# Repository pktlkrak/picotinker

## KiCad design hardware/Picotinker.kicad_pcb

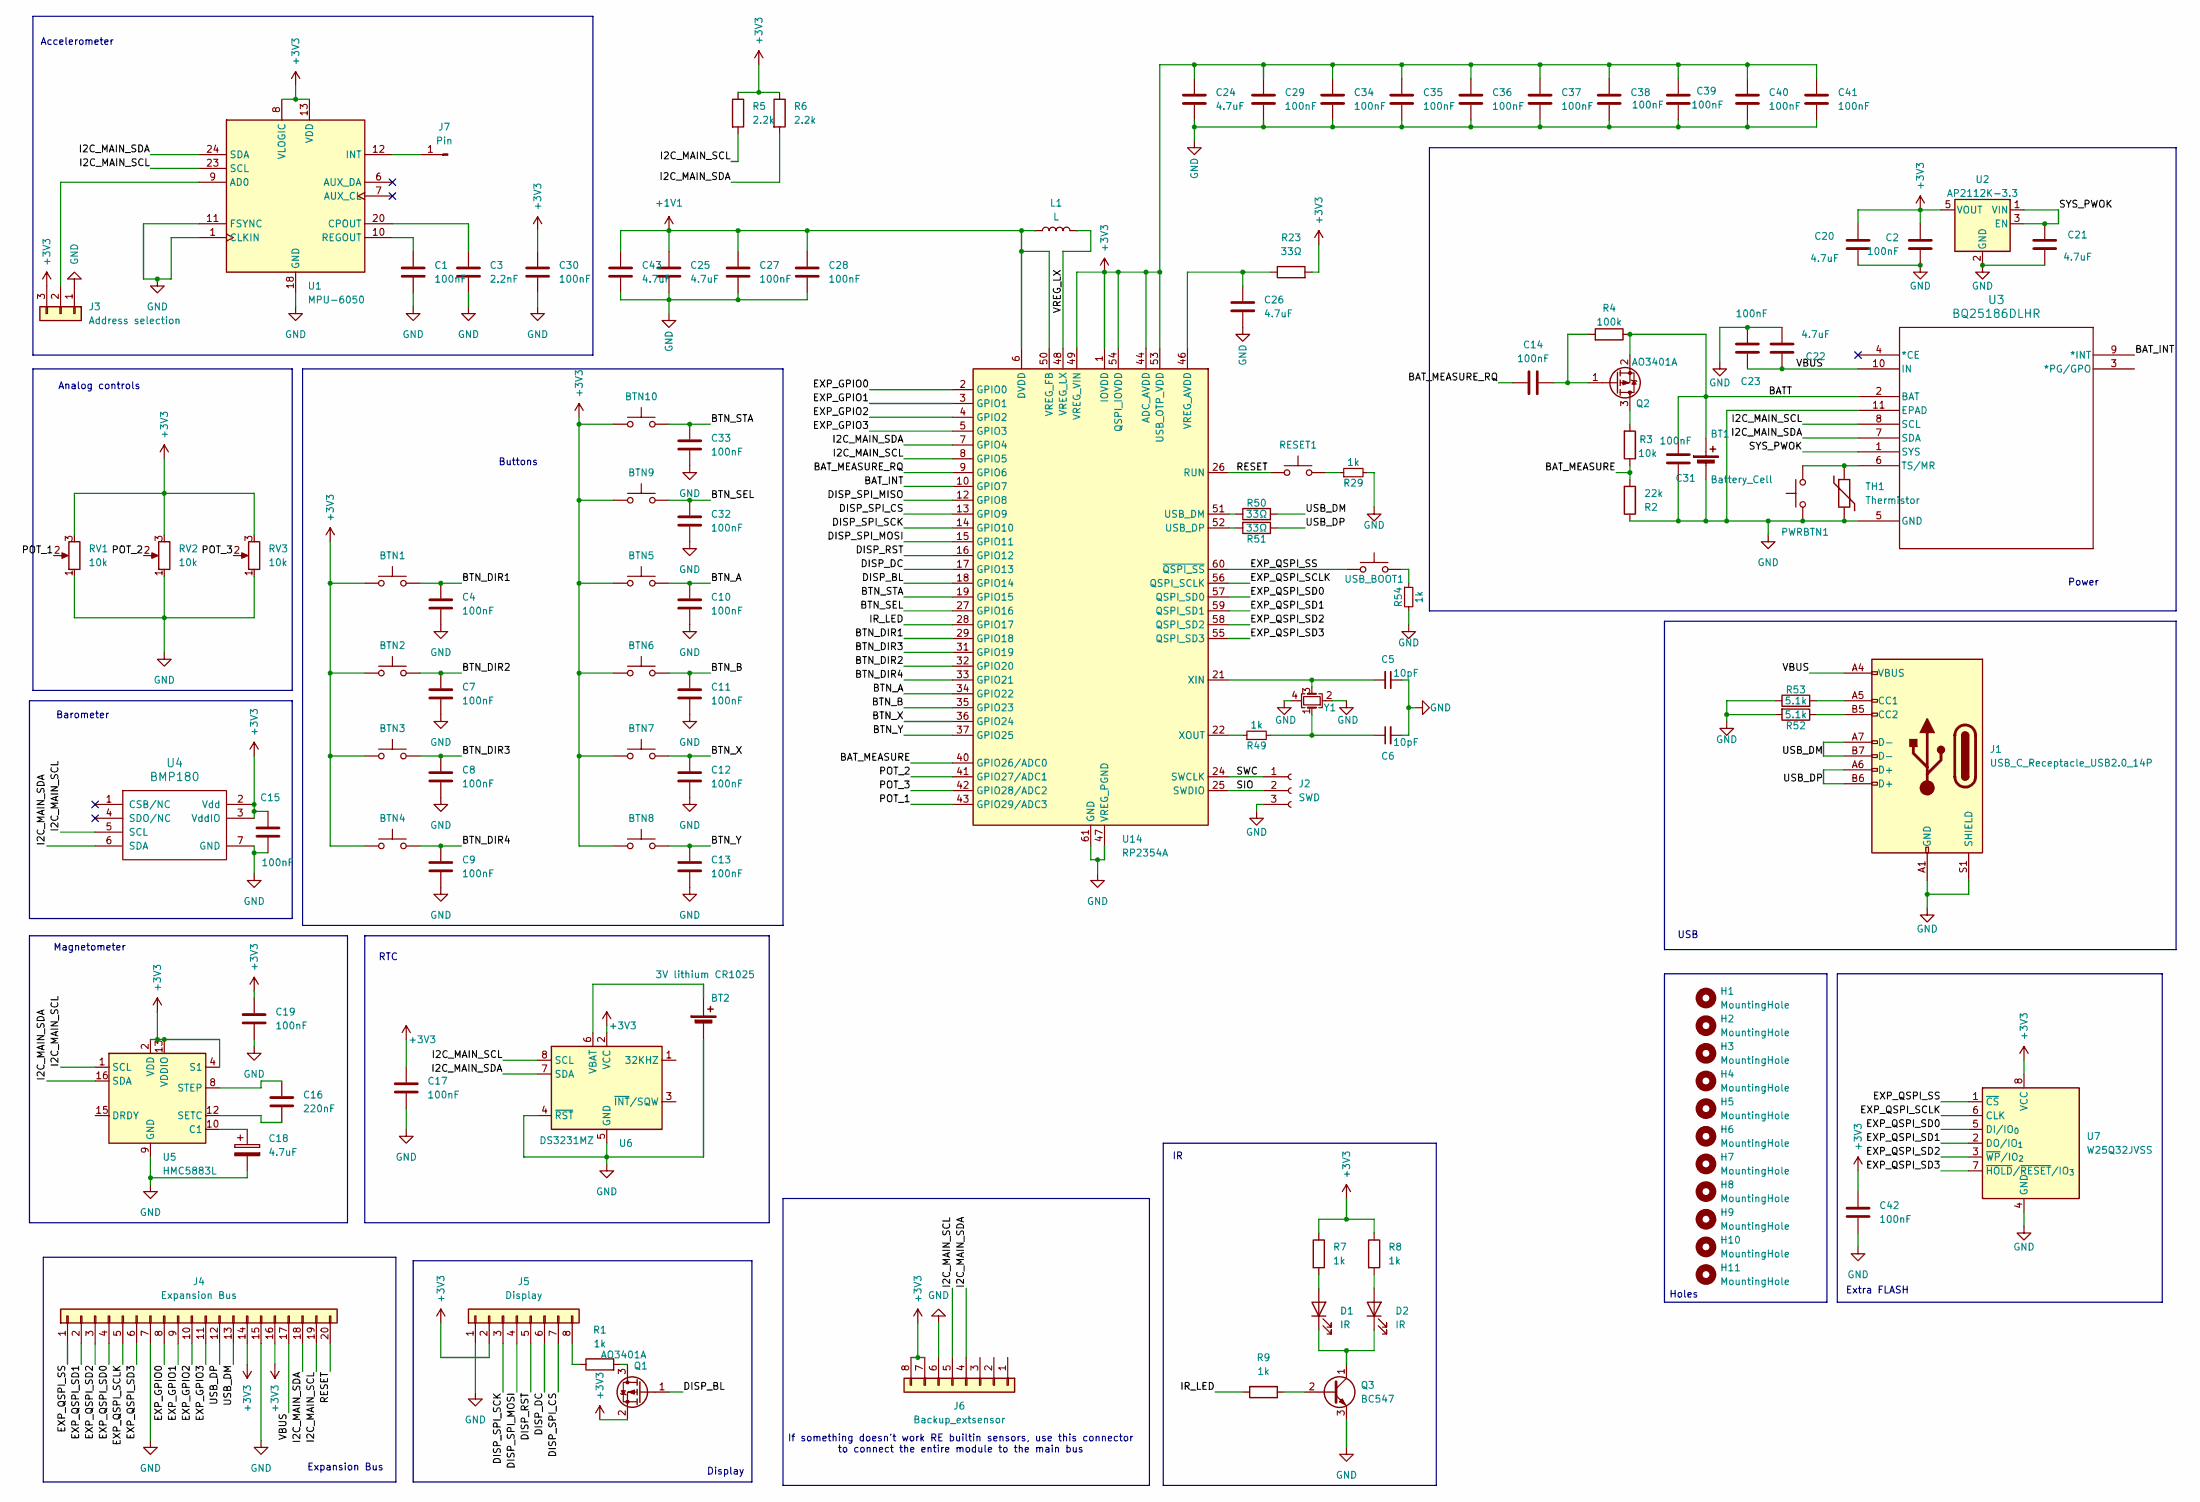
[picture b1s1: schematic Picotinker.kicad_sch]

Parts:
BT1: Battery_Cell; PinHeader_1x02_P2.00mm_Vertical
BT2: 3V lithium CR1025; BatteryHolder_LINX_BAT-HLD-012-SMT
BTN1, BTN2, BTN3, BTN4, BTN5, BTN6, BTN7, BTN8, BTN9, BTN10: SW_Push; SW_PUSH_6mm; MPN KMR241G LFS
C1, C4, C7, C8, C9, C10, C11, C12, C13, C14, C15, C17, C19, C23, C31, C32, C33: 100nF; C_0603_1608Metric
C2, C27, C28, C29, C30, C34, C35, C36, C37, C38, C39, C40, C41, C42: 100nF; C_0603_1608Metric; MPN CL05B104KA5NNNC
C3: 2.2nF; C_0603_1608Metric
C5, C6: 10pF; C_0603_1608Metric; MPN CL10C100JB8NFNC
C16: 220nF; C_0603_1608Metric
C18, C20, C21, C22: 4.7uF; C_1206_3216Metric
C24, C25, C26, C43: 4.7uF; C_0603_1608Metric; MPN GRM155D80E475ME47J
D1, D2: IR; LED_D3.0mm
H1, H2, H3, H4, H5, H6, H7, H8, H9, H10, H11: MountingHole; MountingHole_2.2mm_M2
J1: USB_C_Receptacle_USB2.0_14P; USB_C_Receptacle_XKB_U262-16XN-4BVC11; MPN TYPE-C-31-M-14
J2: SWD; PinHeader_1x03_P2.54mm_Vertical
J3: Address selection; SolderJumper-3_P2.0mm_Open_TrianglePad1.0x1.5mm
J4: Expansion Bus; PinHeader_1x21_P2.54mm_Vertical
J5: Display; PinHeader_1x09_P2.54mm_Vertical
J6: Backup_extsensor; PinHeader_1x08_P2.54mm_Vertical
J7: Pin; Pin_D1.0mm_L10.0mm
L1: L; R_0805_2012Metric; MPN AOTA-B201610S3R3-101-T
PWRBTN1: SW_Push; SW_Tactile_SPST_Angled_PTS645Vx58-2LFS; MPN KMR241G LFS
Q1, Q2: AO3401A; SOT-23
Q3: BC547; SOT-23
R1, R7, R8, R9: 1k; R_0603_1608Metric
R2: 22k; R_0603_1608Metric
R3: 10k; R_0603_1608Metric
R4: 100k; R_0603_1608Metric
R5, R6: 2.2k; R_0603_1608Metric
R23, R50, R51: 33Ω; R_0603_1608Metric; MPN RC0402FR-0733RL
R29, R49, R54: 1k; R_0603_1608Metric; MPN RT0603FRE101KL
R52, R53: 5.1k; R_0603_1608Metric; MPN RC0402FR-075K1L
RESET1: SW_Push; SW_Push_1P1T_NO_CK_KSC6xxG; MPN KMR241G LFS
RV1, RV2: 10k; Potentiometer_Piher_T-16L_Single_Vertical_Hole
RV3: 10k; Potentiometer_Bourns_PTA4543_Single_Slide
TH1: Thermistor; PinHeader_1x02_P2.00mm_Vertical
U1: MPU-6050; InvenSense_QFN-24_4x4mm_P0.5mm
U2: AP2112K-3.3; SOT-23-5; MPN AP2112K-3.3TRG1
U3: BQ25186DLHR; WSON10_2P2X2_TEX
U4: BMP180
U5: HMC5883L; LGA-16_3x3mm_P0.5mm
U6: DS3231MZ; SOIC-8_3.9x4.9mm_P1.27mm
U7: W25Q32JVSS; SOIC-8_5.3x5.3mm_P1.27mm
U14: RP2354A; QFN-60-1EP_7x7mm_P0.4mm_EP3.4x3.4mm; MPN SC1511(13)-A4
USB_BOOT1: SW_Push; SW_Push_1P1T_NO_CK_KSC6xxG; MPN KMR241G LFS
Y1: Crystal; Crystal_SMD_3225-4Pin_3.2x2.5mm; MPN ABM8-272-T3

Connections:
+1V1: C25.1, C27.2, C28.2, C43.1, L1.1, U14.6 (DVDD), U14.23 (DVDD), U14.39 (DVDD), U14.50 (VREG_FB)
+3V3: BTN1.1, BTN2.1, BTN3.1, BTN4.1, BTN5.1, BTN6.1, BTN7.1, BTN8.1, BTN9.1, BTN10.1, C2.2, C15.1, C17.1, C19.1, C20.1, C24.1, C29.2, C30.1, C34.2, C35.2, C36.2, C37.2, C38.2, C39.2, C40.2, C41.2, C42.1, J3.3, J4.14, J4.16, J5.2, J6.7, J6.8, Q1.2 (S), R5.1, R6.1, R7.1, R8.1, R23.2, RV1.3, RV2.3, RV3.3, U1.8 (VLOGIC), U1.13 (VDD), U2.5 (VOUT), U4.2 (Vdd), U4.3 (VddIO), U5.2 (VDD), U5.4 (S1), U5.13 (VDDIO), U6.2 (VCC), U7.8 (VCC), U14.1 (IOVDD), U14.11 (IOVDD), U14.20 (IOVDD), U14.30 (IOVDD), U14.38 (IOVDD), U14.44 (ADC_AVDD), U14.45 (IOVDD), U14.49 (VREG_VIN), U14.53 (USB_OTP_VDD), U14.54 (QSPI_IOVDD)
/BATT: BT1.1 (+), C31.2, Q2.2 (S), R4.1, U3.2 (BAT)
/BAT_INT: U3.9 (*INT), U14.10 (GPIO7)
/BAT_MEASURE: R2.2, R3.1, U14.40 (GPIO26/ADC0)
/BAT_MEASURE_RQ: C14.2, U14.9 (GPIO6)
/BTN_A: BTN5.2, C10.2, U14.34 (GPIO22)
/BTN_B: BTN6.2, C11.2, U14.35 (GPIO23)
/BTN_DIR1: BTN1.2, C4.2, U14.29 (GPIO18)
/BTN_DIR2: BTN2.2, C7.2, U14.32 (GPIO20)
/BTN_DIR3: BTN3.2, C8.2, U14.31 (GPIO19)
/BTN_DIR4: BTN4.2, C9.2, U14.33 (GPIO21)
/BTN_SEL: BTN9.2, C32.2, U14.27 (GPIO16)
/BTN_STA: BTN10.2, C33.2, U14.19 (GPIO15)
/BTN_X: BTN7.2, C12.2, U14.36 (GPIO24)
/BTN_Y: BTN8.2, C13.2, U14.37 (GPIO25)
/DISP_BL: Q1.1 (G), U14.18 (GPIO14)
/DISP_DC: J5.6, U14.17 (GPIO13)
/DISP_RST: J5.5, U14.16 (GPIO12)
/DISP_SPI_CS: J5.7, U14.13 (GPIO9)
/DISP_SPI_MISO: U14.12 (GPIO8)
/DISP_SPI_MOSI: J5.4, U14.15 (GPIO11)
/DISP_SPI_SCK: J5.3, U14.14 (GPIO10)
/EXP_GPIO0: J4.8, U14.2 (GPIO0)
/EXP_GPIO1: J4.9, U14.3 (GPIO1)
/EXP_GPIO2: J4.10, U14.4 (GPIO2)
/EXP_GPIO3: J4.11, U14.5 (GPIO3)
/EXP_QSPI_SCLK: J4.5, U7.6 (CLK), U14.56 (QSPI_SCLK)
/EXP_QSPI_SD0: J4.4, U7.5 (DI/IO_{0}), U14.57 (QSPI_SD0)
/EXP_QSPI_SD1: J4.2, U7.2 (DO/IO_{1}), U14.59 (QSPI_SD1)
/EXP_QSPI_SD2: J4.3, U7.3 (~WP/IO_{2}), U14.58 (QSPI_SD2)
/EXP_QSPI_SD3: J4.6, U7.7 (~HOLD/~RESET/IO_{3}), U14.55 (QSPI_SD3)
/EXP_QSPI_SS: J4.1, U7.1 (~CS), U14.60 (~QSPI_SS), USB_BOOT1.1
/I2C_MAIN_SCL: J4.19, J6.5, R5.2, U1.23 (SCL), U3.8 (SCL), U4.5 (SCL), U5.1 (SCL), U6.8 (SCL), U14.8 (GPIO5)
/I2C_MAIN_SDA: J4.18, J6.4, R6.2, U1.24 (SDA), U3.7 (SDA), U4.6 (SDA), U5.16 (SDA), U6.7 (SDA), U14.7 (GPIO4)
/IR_LED: R9.1, U14.28 (GPIO17)
/POT_1: RV1.2, U14.43 (GPIO29/ADC3)
/POT_2: RV2.2, U14.41 (GPIO27/ADC1)
/POT_3: RV3.2, U14.42 (GPIO28/ADC2)
/RESET: J4.20, RESET1.1, U14.26 (RUN)
/SIO: J2.2, U14.25 (SWDIO)
/SWC: J2.1, U14.24 (SWCLK)
/SYS_PWOK: C21.1, U2.1 (VIN), U2.3 (EN), U3.1 (SYS)
/USB_DM: J1.A7 (D-), J1.B7 (D-), J4.13, R50.2
/USB_DP: J1.A6 (D+), J1.B6 (D+), J4.12, R51.1
/VBUS: C22.1, C23.1, J1.A4 (VBUS), J1.A9 (VBUS), J1.B4 (VBUS), J1.B9 (VBUS), J4.17, U3.10 (IN)
/VREG_LX: L1.2, U14.48 (VREG_LX)
GND: BT1.2 (-), BT2.2 (-), C1.2, C2.1, C3.2, C4.1, C5.1, C6.2, C7.1, C8.1, C9.1, C10.1, C11.1, C12.1, C13.1, C15.2, C17.2, C18.2, C19.2, C20.2, C21.2, C22.2, C23.2, C24.2, C25.2, C26.2, C27.1, C28.1, C29.1, C30.2, C31.1, C32.1, C33.1, C34.1, C35.1, C36.1, C37.1, C38.1, C39.1, C40.1, C41.1, C42.2, C43.2, J1.A1 (GND), J1.A12 (GND), J1.B1 (GND), J1.B12 (GND), J1.S1 (SHIELD), J2.3, J3.1, J4.7, J4.15, J5.1, J6.6, PWRBTN1.1, Q3.3 (E), R2.1, R29.2, R52.2, R53.1, R54.2, RV1.1, RV2.1, RV3.1, TH1.2, U1.1 (CLKIN), U1.11 (FSYNC), U1.18 (GND), U2.2 (GND), U3.5 (GND), U3.11 (EPAD), U4.7 (GND), U5.9 (GND), U5.11 (GND), U6.4 (~RST), U6.5 (GND), U7.4 (GND), U14.47 (VREG_PGND), U14.61 (GND), Y1.2, Y1.4
unnamed: BT2.1 (+), U6.6 (VBAT)
unnamed: C6.1, R49.2, Y1.1
unnamed: D1.2 (A), R7.2
unnamed: D1.1 (K), D2.1 (K), Q3.1 (C)
unnamed: D2.2 (A), R8.2
unnamed: J1.A5 (CC1), R53.2
unnamed: J1.B5 (CC2), R52.1
unnamed: J3.2, U1.9 (AD0)
unnamed: J5.8, R1.1
unnamed: J7.1 (Pin_1_1), U1.12 (INT)
unnamed: Q1.3 (D), R1.2
unnamed: Q2.3 (D), R3.2
unnamed: C14.1, Q2.1 (G), R4.2
unnamed: Q3.2 (B), R9.2
unnamed: R29.1, RESET1.2
unnamed: R54.1, USB_BOOT1.2
unnamed: C3.1, U1.20 (CPOUT)
unnamed: C1.1, U1.10 (REGOUT)
unnamed: PWRBTN1.2, TH1.1, U3.6 (TS/MR)
unnamed: C18.1, U5.10 (C1)
unnamed: C16.2, U5.12 (SETC)
unnamed: C16.1, U5.8 (STEP)
unnamed: R50.1, U14.51 (USB_DM)
unnamed: R51.2, U14.52 (USB_DP)
unnamed: C26.1, R23.1, U14.46 (VREG_AVDD)
unnamed: C5.2, U14.21 (XIN), Y1.3
unnamed: R49.1, U14.22 (XOUT)

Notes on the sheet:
Extra FLASH
Barometer
Display
Expansion Bus
RTC
Magnetometer
If something doesn't work RE builtin sensors, use this connector to connect the entire module to the main bus
Buttons
Analog controls
USB
Power
Holes
Accelerometer

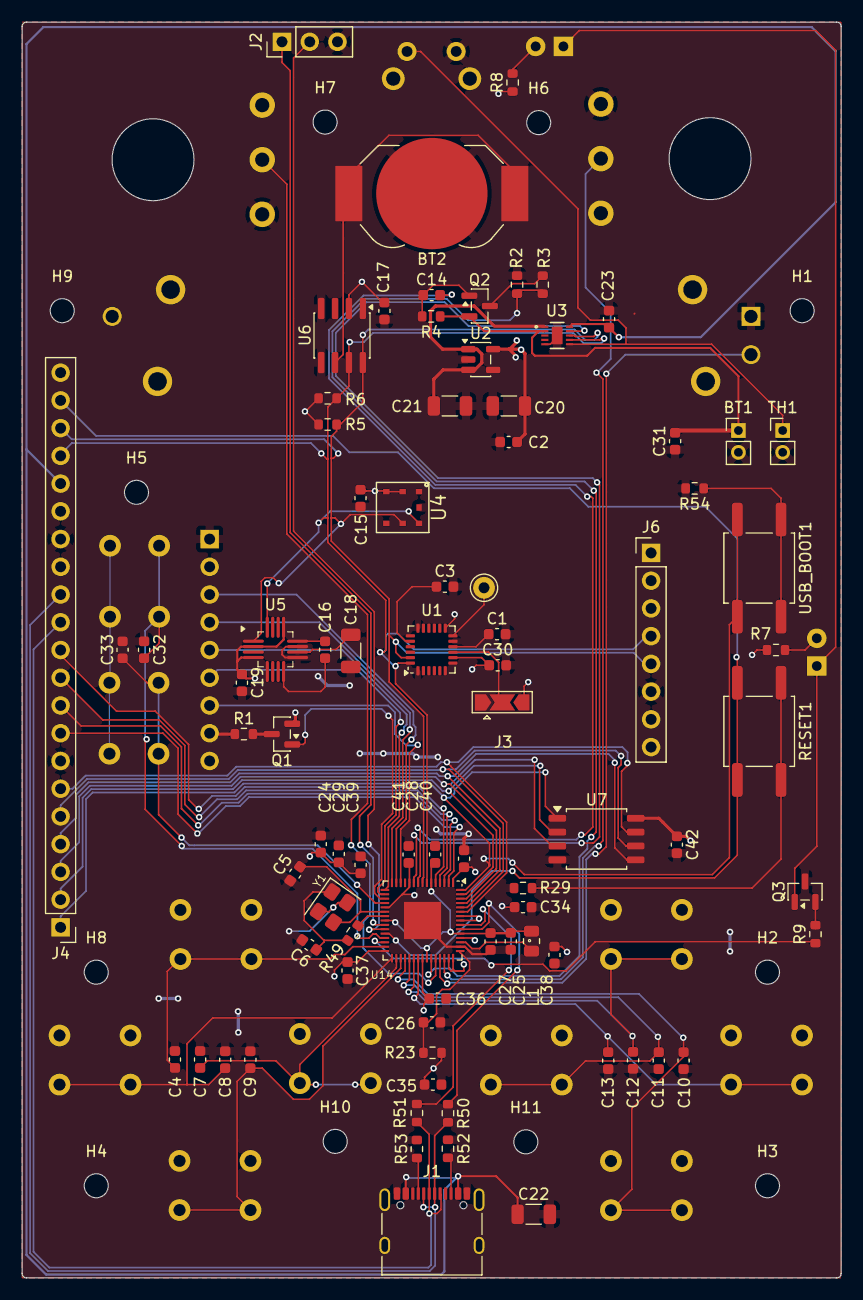
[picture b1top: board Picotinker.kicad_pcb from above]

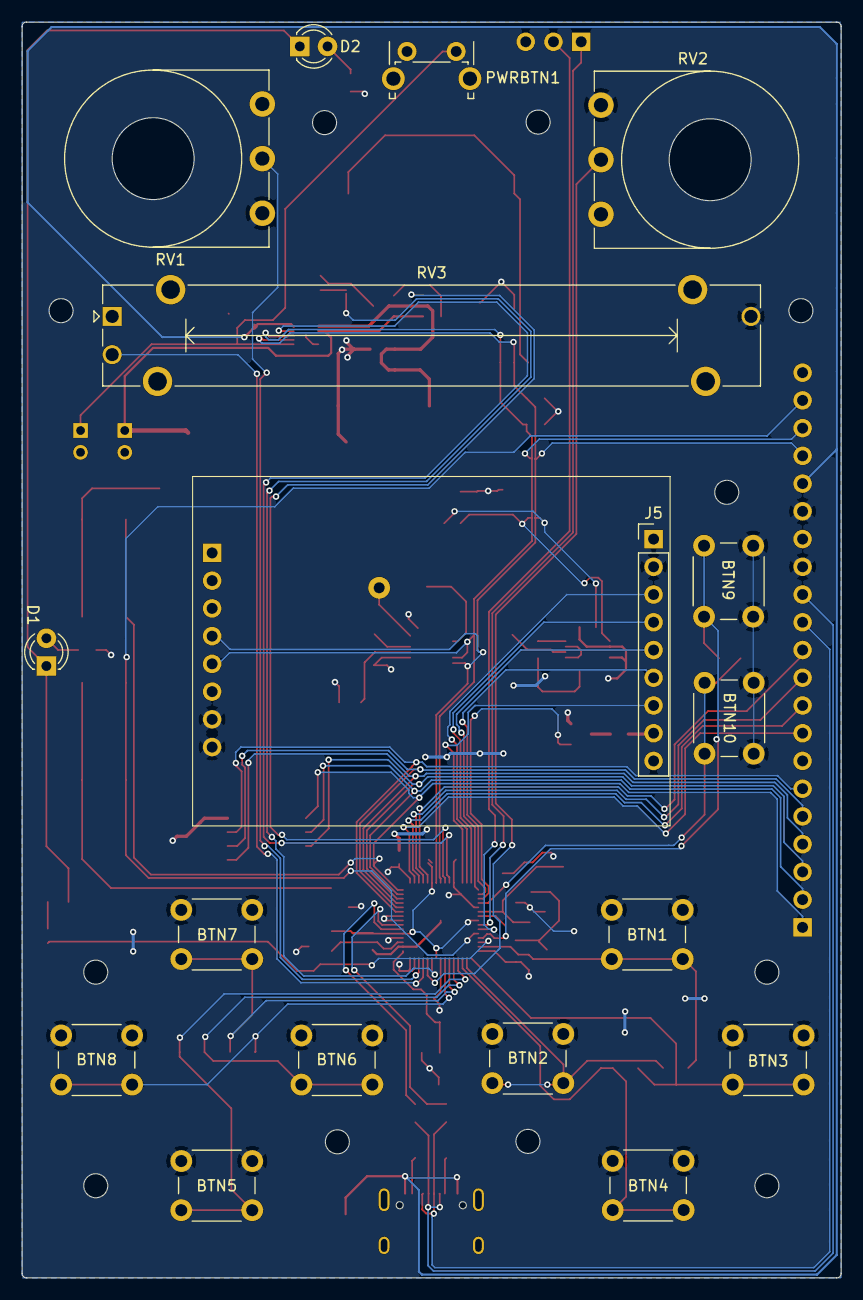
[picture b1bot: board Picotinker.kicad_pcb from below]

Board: 2 copper layers, 75.0 x 115.0 mm, 111 parts (17 on the bottom side), 74 nets.

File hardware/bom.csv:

Designator,Footprint,Quantity,Value,LCSC Part #
BT2,BatteryHolder_LINX_BAT-HLD-012-SMT,1,3V lithium CR1025,C5189234
"C1, C10, C11, C12, C13, C14, C15, C17, C19, C23, C31, C32, C33, C4, C7, C8, C9",0603,17,100nF,C14663
C16,0603,1,220nF,C21120
"C18, C20, C21, C22",1206,4,4.7uF,C29823
"C2, C27, C28, C29, C30, C34, C35, C36, C37, C38, C39, C40, C41, C42",0603,14,100nF,C14663
"C24, C25, C26",0603,3,4.7uF,C19666
C3,0603,1,2.2nF,C1604
"C5, C6",0603,2,10pF,C1634
J1,USB_C_Receptacle_XKB_U262-16XN-4BVC11,1,USB_C_Receptacle_USB2.0_14P,C22383468
L1,0805,1,L,C42411119
"Q1, Q2",SOT-23,2,AO3401A,C15127
Q3,SOT-23,1,BC547,C2145
"R1, R7, R8",0603,3,1k,C21190
R2,0603,1,22k,C31850
"R23, R50, R51",0603,3,33Ω,C23140
"R29, R49, R54",0603,3,1k,C21190
R3,0603,1,10k,C25804
R4,0603,1,100k,C25803
"R5, R6",0603,2,2.2k,C4190
"R52, R53",0603,2,5.1k,C23186
R9,0603,1,1k,C21190
"RESET1, USB_BOOT1",SW_Push_1P1T_NO_CK_KSC6xxG,2,SW_Push,C226344
U14,QFN-60-1EP_7x7mm_P0.4mm_EP3.4x3.4mm,1,RP2354A,C41378174
U2,SOT-23-5,1,AP2112K-3.3,C51118
U3,WSON10_2P2X2_TEX,1,BQ25186DLHR,C44639442
U6,SOIC-8_3.9x4.9mm_P1.27mm,1,DS3231MZ,C722467
Y1,Crystal_SMD_3225-4Pin_3.2x2.5mm,1,Crystal,C20625731
